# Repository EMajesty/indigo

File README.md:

# indigo

## features

 * 52 keys
 * Positive/neutral/negative tilt
 * Tenting
 * Middle piece with space for:
   * Trackball
   * Trackpad
   * Numpad
   * Raspberry Pi

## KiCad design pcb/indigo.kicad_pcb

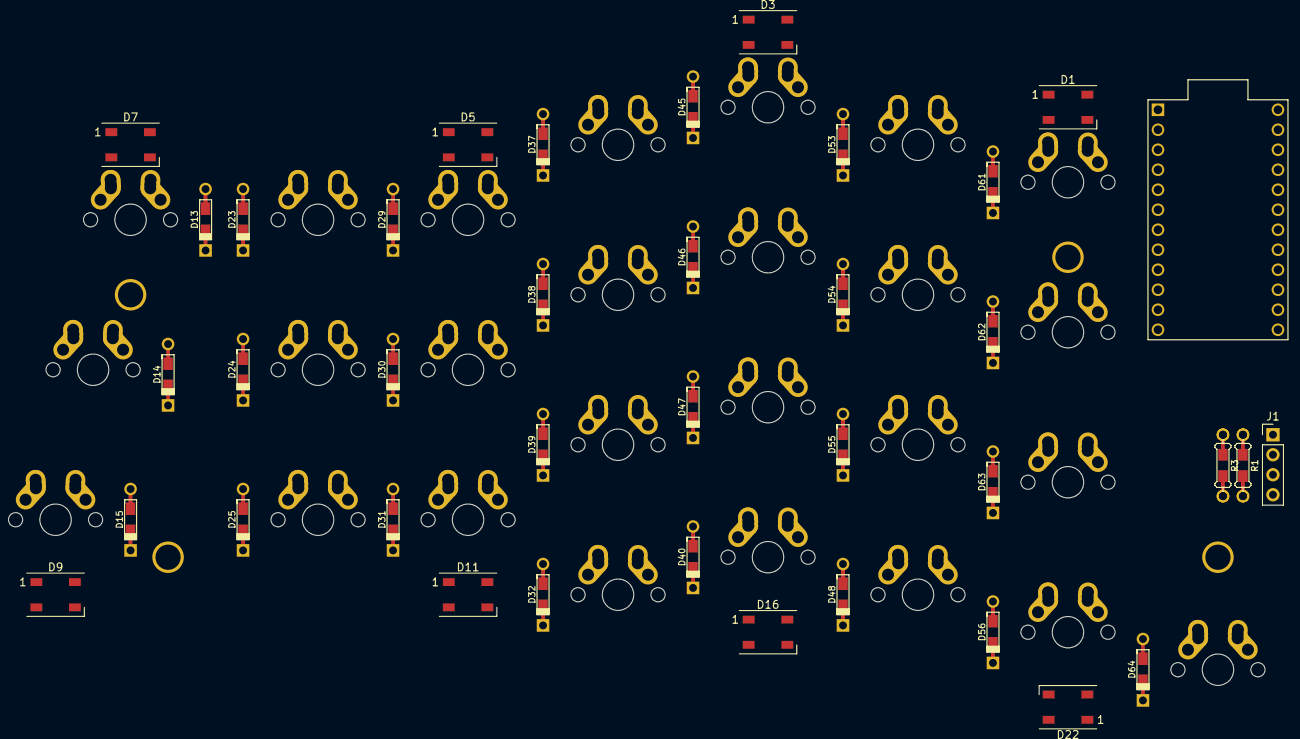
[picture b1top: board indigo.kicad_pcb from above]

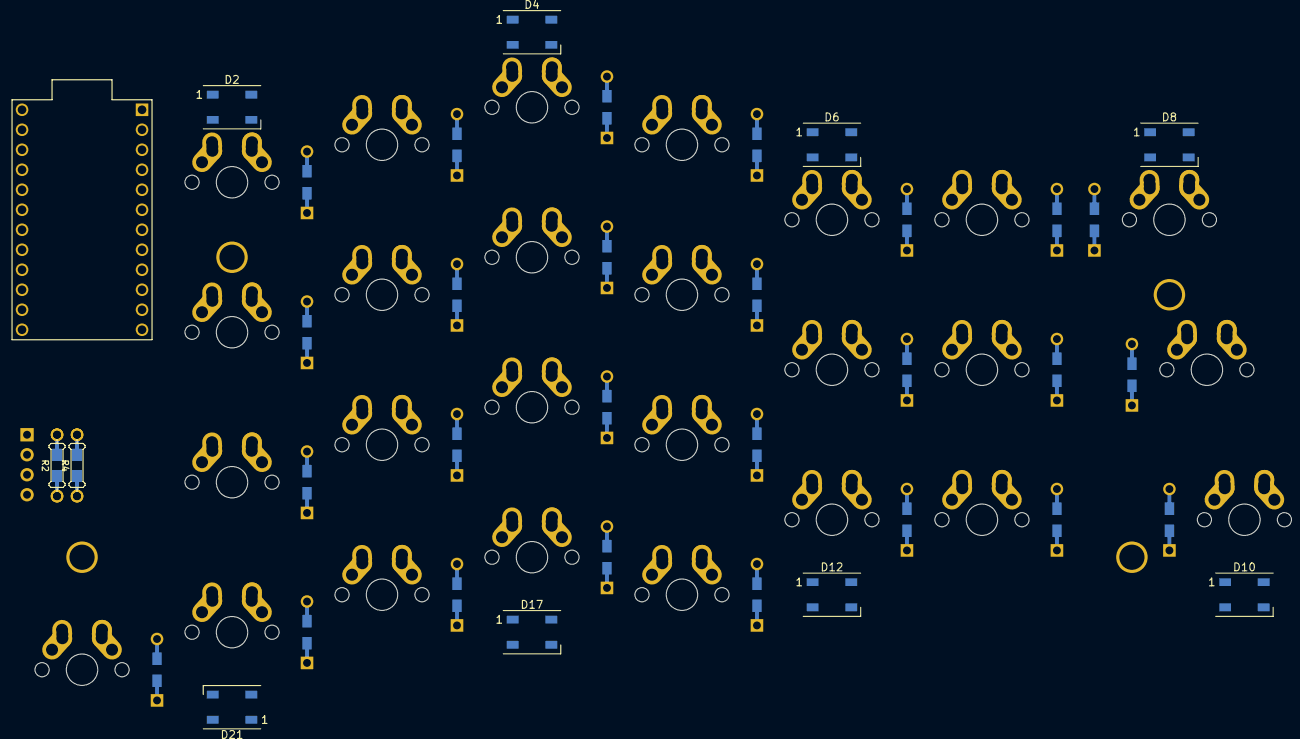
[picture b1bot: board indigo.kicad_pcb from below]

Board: 2 copper layers, 78 parts (8 on the bottom side), 56 nets, no tracks yet.

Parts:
D1, D2, D3, D4, D5, D6, D7, D8, D9, D10, D11, D12, D16, D17, D21, D22: WS2812B; LED_WS2812B_PLCC4_5.0x5.0mm_P3.2mm
D13, D14, D15, D23, D24, D25, D29, D30, D31, D32, D37, D38, D39, D40, D45, D46, D47, D48, D53, D54, D55, D56, D61, D62, D63, D64: D; Diode-dual
H1, H2, H3, H4: MountingHole; HOLE_M3
J1: Conn_01x04; PinHeader_1x04_P2.54mm_Vertical
R1, R3: R; Resistor-Hybrid
R2, R4: R; Resistor-Hybrid-Back
SW1, SW2, SW3, SW4, SW5, SW6, SW7, SW8, SW9, SW10, SW11, SW12, SW13, SW14, SW15, SW16, SW17, SW18, SW19, SW20, SW21, SW22, SW23, SW24, SW25, SW26: SW_Push; Hybrid_PCB_100H_Dual_hole-nosilk
U1: ProMicro

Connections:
/C1: SW1.1, SW2.1, SW3.1, U1.11
/C2: SW4.1, SW5.1, SW6.1, U1.12
/C3: SW7.1, SW8.1, SW9.1, SW10.1, U1.13
/C4: SW11.1, SW12.1, SW13.1, SW14.1, U1.14
/C5: SW15.1, SW16.1, SW17.1, SW18.1, U1.15
/C6: SW19.1, SW20.1, SW21.1, SW22.1, U1.16
/C7: SW23.1, SW24.1, SW25.1, SW26.1, U1.17
/LED_PIN: D1.4, D2.4, U1.20
/R1: D13.1, D23.1, D29.1, D37.1, D45.1, D53.1, D61.1, U1.7
/R2: D14.1, D24.1, D30.1, D38.1, D46.1, D54.1, D62.1, U1.8
/R3: D15.1, D25.1, D31.1, D39.1, D47.1, D55.1, D63.1, U1.9
/R4: D32.1, D40.1, D48.1, D56.1, D64.1, U1.10
GND: D1.3, D2.3, D3.3, D4.3, D5.3, D6.3, D7.3, D8.3, D9.3, D10.3, D11.3, D12.3, D16.3, D17.3, D21.3, D22.3, J1.4, R1.2, R2.2, R3.2, R4.2, U1.3, U1.4, U1.23
unnamed: D1.2, D3.4
unnamed: D2.2, D4.4
unnamed: D3.2, D5.4
unnamed: D4.2, D6.4
unnamed: D5.2, D7.4
unnamed: D6.2, D8.4
unnamed: D7.2, D9.4
unnamed: D10.2, D12.4
unnamed: D8.2, D10.4
unnamed: D11.2, D16.4
unnamed: D9.2, D11.4
unnamed: D12.2, D17.4
unnamed: D13.2, SW1.2
unnamed: D14.2, SW2.2
unnamed: D15.2, SW3.2
unnamed: D16.2, D21.4
unnamed: D17.2, D22.4
unnamed: D23.2, SW4.2
unnamed: D24.2, SW5.2
unnamed: D25.2, SW6.2
unnamed: D29.2, SW7.2
unnamed: D30.2, SW8.2
unnamed: D31.2, SW9.2
unnamed: D32.2, SW10.2
unnamed: D37.2, SW11.2
unnamed: D38.2, SW12.2
unnamed: D39.2, SW13.2
unnamed: D40.2, SW14.2
unnamed: D45.2, SW15.2
unnamed: D46.2, SW16.2
unnamed: D47.2, SW17.2
unnamed: D48.2, SW18.2
unnamed: D53.2, SW19.2
unnamed: D54.2, SW20.2
unnamed: D55.2, SW21.2
unnamed: D56.2, SW22.2
unnamed: D61.2, SW23.2
unnamed: D62.2, SW24.2
unnamed: D63.2, SW25.2
unnamed: D64.2, SW26.2
unnamed: J1.2, R3.1, R4.1, U1.5
unnamed: J1.3, R1.1, R2.1, U1.6
VCC: D1.1, D2.1, D3.1, D4.1, D5.1, D6.1, D7.1, D8.1, D9.1, D10.1, D11.1, D12.1, D16.1, D17.1, D21.1, D22.1, J1.1, U1.21

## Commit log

2021-02-25 readme
2021-02-25 initial kicad stuff
2021-02-25 gitignore
2021-02-25 ignore better
2021-02-26 pcb started
2021-02-28 pcb, features
